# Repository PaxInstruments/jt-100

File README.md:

# Pax Instruments
# JT-100 Junction Thermometer

[Pax Instruments Template Module](<link to store page>)

## Overview
This device is used to measure the temperature of your soldering iron tip and is packaged as a learn to surface mount solder kit.

## Repository Contents
- __Datasheets__ - Datasheets for relevant components and parts
- __Electronics__ - All PCB and schematic design files
- __Enclosure__ - Enclosure 3D design files
- __Firmware__ - Firmware, libraries, and examples
- __Production__ - Manufacturing resources
- __Resources__ - Other resources

## Product Versions

## License Information
```
Place the license statement here
```

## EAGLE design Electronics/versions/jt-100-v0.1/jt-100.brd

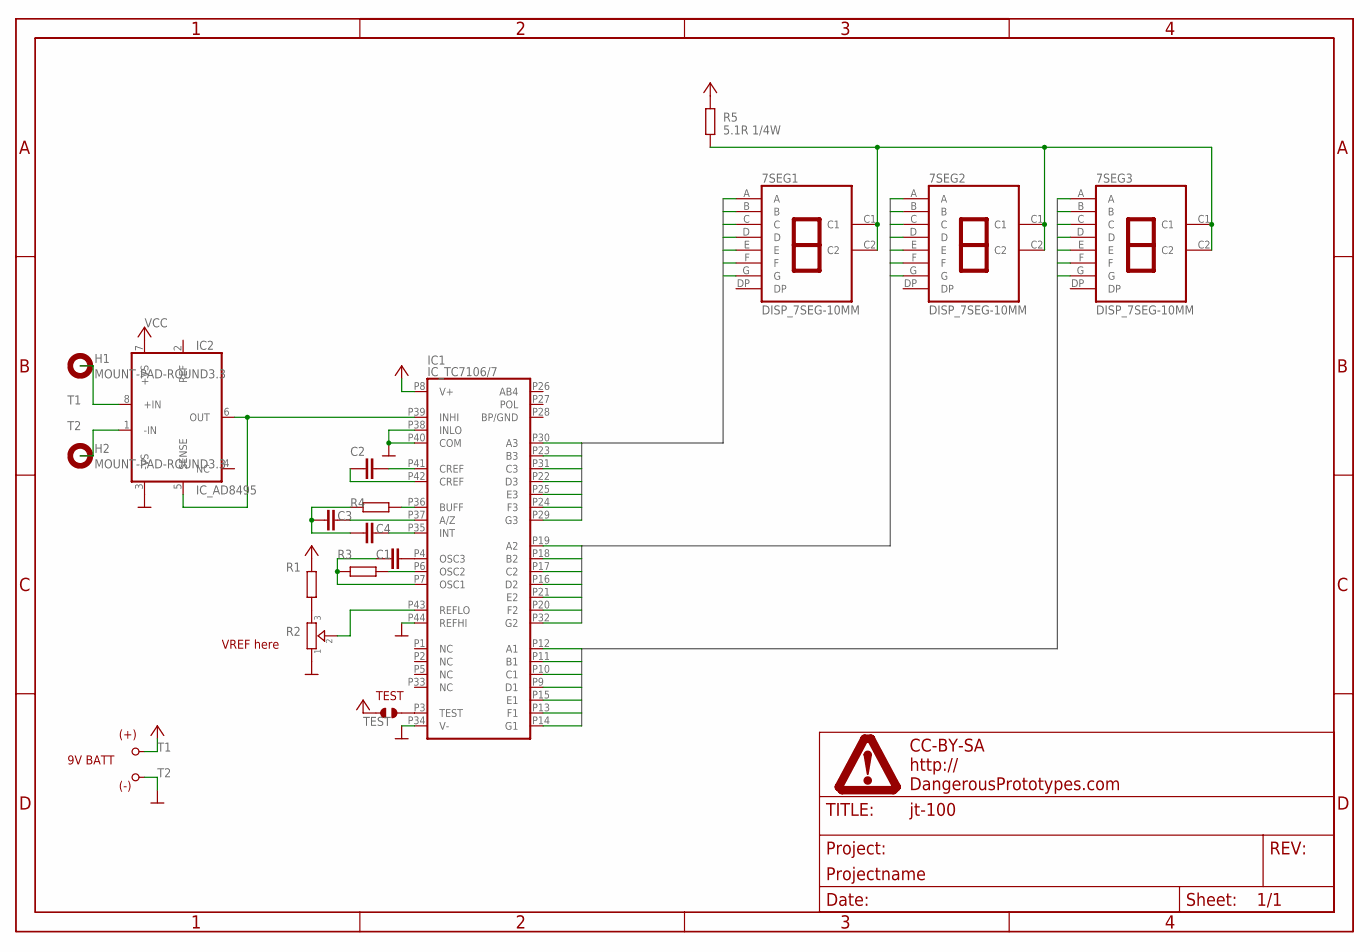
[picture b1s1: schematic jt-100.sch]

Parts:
7SEG1, 7SEG2, 7SEG3: DISP_7SEG-10MM; DISP_7SEG_KTS_4817CKR-P; MPN LTS-4817CKR-P
C1, C2, C3, C4: CAPACITOR_NPOL-1206; C1206
H1, H2: MOUNT-PAD-ROUND3.3; 3,3-PAD
IC1: IC_TC7106/7; TQFP-44; MPN TC7106CKW
IC2: IC_AD8495; MSOP8; MPN AD8495ARMZ
R1, R3, R4: RESISTOR-1206; R1206
R2: TRIMMER-3314G; TRIMMER_3314G
R5: 5.1R 1/4W; R1206
T1: PAD_TERMINAL-1.02MM_SQUARE; CON_PAD_SQUARE_1.02MM
T2: PAD_TERMINAL-1.02MM_ROUND; CON_PAD_ROUND_1.02MM
TEST: JUMPER_SOLDER_1X2
U$1: FRAME_DINA4_L; DP_LOGO

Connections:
1S1: 7SEG3.A, IC1.P12 (A1)
1S2: 7SEG3.B, IC1.P11 (B1)
1S3: 7SEG3.C, IC1.P10 (C1)
1S4: 7SEG3.D, IC1.P9 (D1)
1S5: 7SEG3.E, IC1.P15 (E1)
1S6: 7SEG3.F, IC1.P13 (F1)
1S7: 7SEG3.G, IC1.P14 (G1)
10S1: 7SEG2.A, IC1.P19 (A2)
10S2: 7SEG2.B, IC1.P18 (B2)
10S3: 7SEG2.C, IC1.P17 (C2)
10S4: 7SEG2.D, IC1.P16 (D2)
10S5: 7SEG2.E, IC1.P21 (E2)
10S6: 7SEG2.F, IC1.P20 (F2)
10S7: 7SEG2.G, IC1.P32 (G2)
100S1: 7SEG1.A, IC1.P30 (A3)
100S2: 7SEG1.B, IC1.P23 (B3)
100S3: 7SEG1.C, IC1.P31 (C3)
100S4: 7SEG1.D, IC1.P22 (D3)
100S5: 7SEG1.E, IC1.P25 (E3)
100S6: 7SEG1.F, IC1.P24 (F3)
100S7: 7SEG1.G, IC1.P29 (G3)
GND: IC1.P34 (V-), IC1.P38 (INLO), IC1.P40 (COM), IC1.P44 (REFHI), IC2.3 (-VS), R2.1, T2.P
unnamed: IC1.P39 (INHI), IC2.5 (SENSE), IC2.6 (OUT)
unnamed: R1.1, R2.3
unnamed: IC1.P43 (REFLO), R2.2
unnamed: C1.2, IC1.P4 (OSC3)
unnamed: C1.1, IC1.P7 (OSC1), R3.2
unnamed: IC1.P6 (OSC2), R3.1
unnamed: C2.2, IC1.P41 (CREF)
unnamed: C2.1, IC1.P42 (CREF)
unnamed: IC1.P36 (BUFF), R4.1
unnamed: C3.1, C4.1, R4.2
unnamed: C3.2, IC1.P37 (A/Z)
unnamed: C4.2, IC1.P35 (INT)
unnamed: 7SEG1.C1, 7SEG1.C2, 7SEG2.C1, 7SEG2.C2, 7SEG3.C1, 7SEG3.C2, R5.1
unnamed: IC1.P3 (TEST), TEST.2
T1: H1.B3,3, IC2.8 (+IN)
T2: H2.B3,3, IC2.1 (-IN)
VCC: IC1.P8 (V+), IC2.7 (+VS), R1.2, R5.2, T1.P, TEST.1

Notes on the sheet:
9V BATT
(+)
(-)
VREF here
TEST

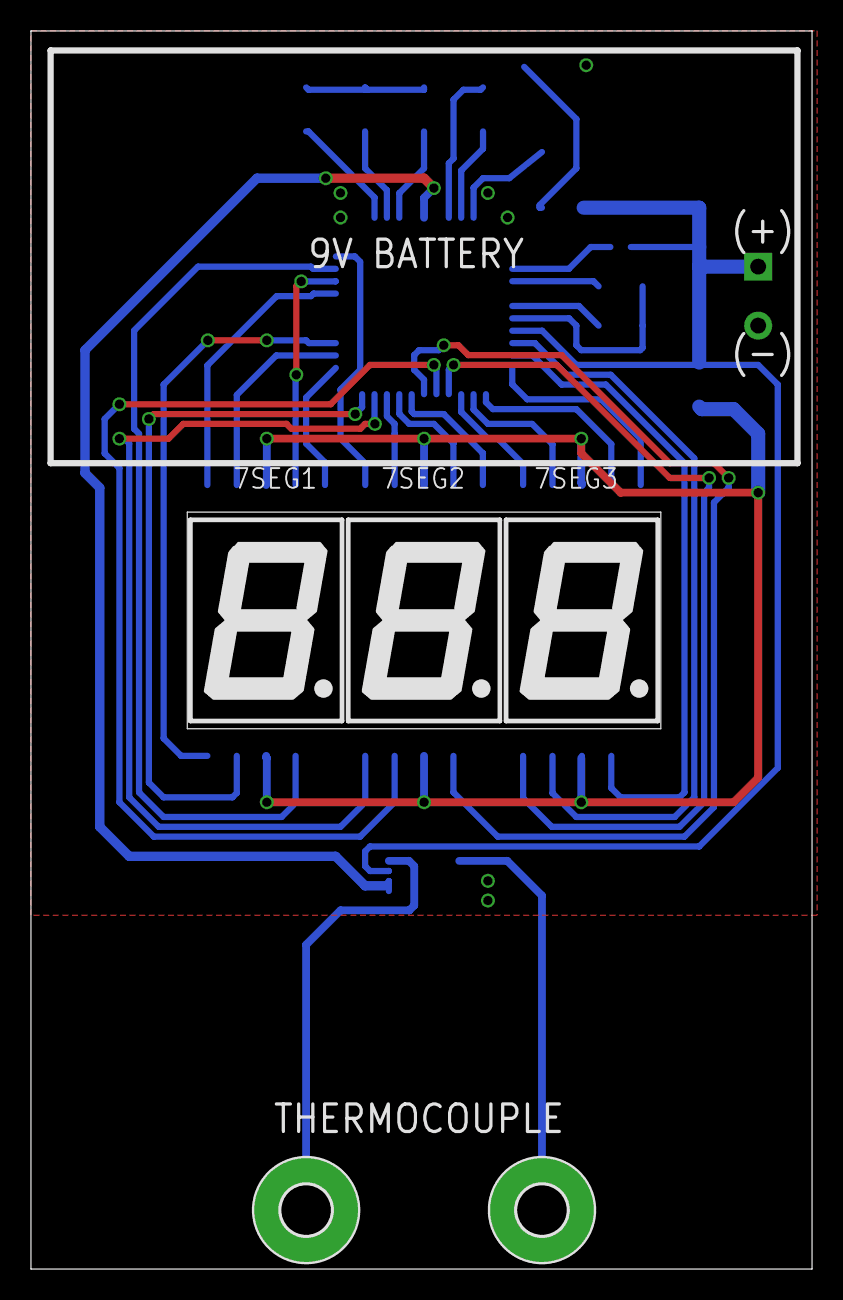
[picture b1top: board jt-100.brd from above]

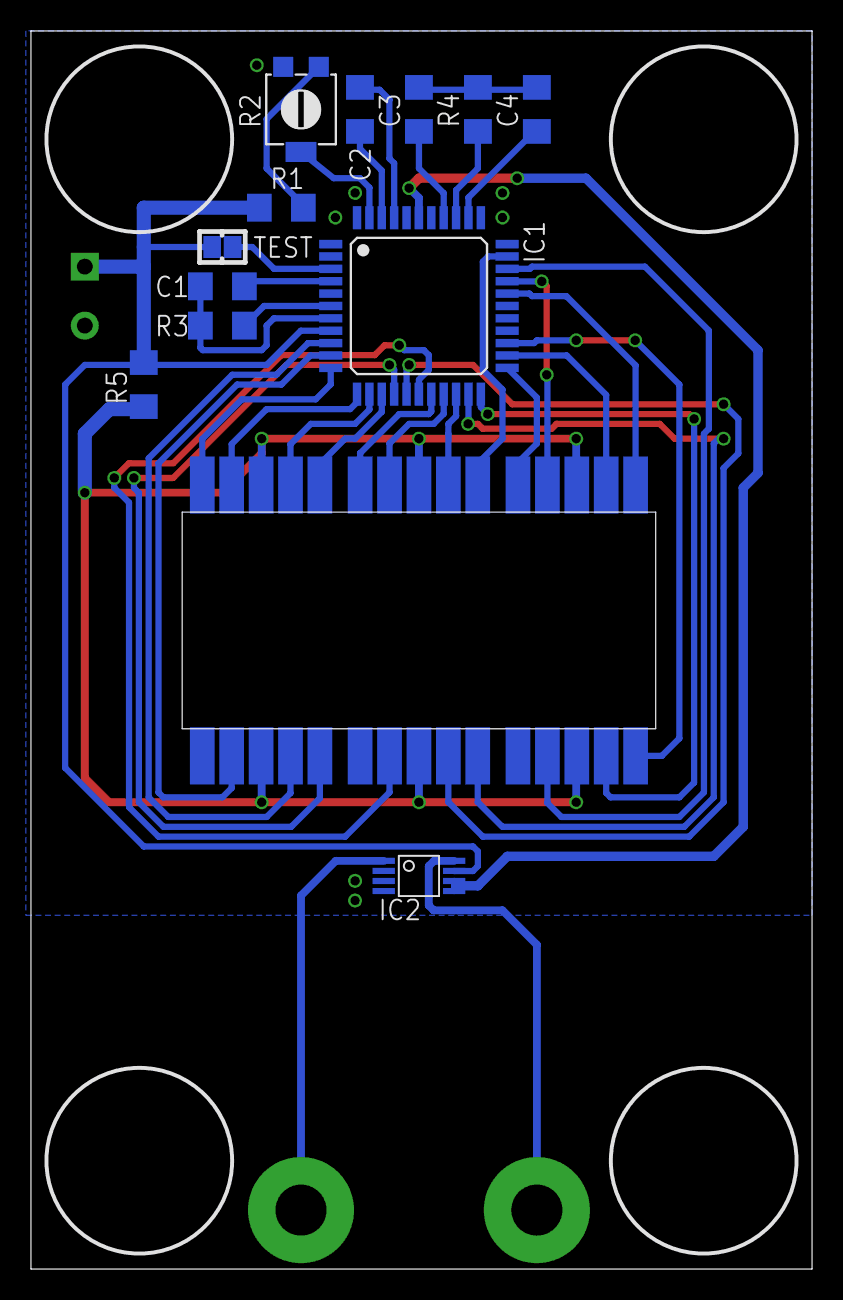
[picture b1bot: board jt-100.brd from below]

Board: 2 copper layers, 50.5 x 80.0 mm, 20 parts (14 on the bottom side), 39 nets.

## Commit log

2015-03-31 Added template files and directory structure. Added datasheets.
2015-03-31 Added Vimark's shematic.
2015-04-01 Added schematic.
2015-04-05 Added gerber files. Updating PCB design.
2015-04-07 Moved versions to folder.
2015-04-07 Removed old gerber zip file.
2015-04-22 Added the 7-segment datasheet.
2015-06-02 Added par numbers to the main components.

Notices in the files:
Electronics/versions/jt-100-v0.1/jt-100.brd:
LICENSE: CC-BY-SA
